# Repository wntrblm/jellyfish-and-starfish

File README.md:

# Jellyfish & Starfish

Jellyfish and Starfish are control boards designed for use with the LumenPnP. Starfish controls the base of the machine including X & Y axes and pneumatics. Jellyfish controls the head of the machine including the Z, A, and B axes.

## No support

Jellyfish and Starfish were made for Winterbloom's internal use cases and we don't have the resources to provide support. While we hope that this repository contains useful information for you, please note that issues and pull requests may go unanswered or may be closed without reply.

## License

Jellyfish and Starfish are open source, however, licensing a project like this is a little complicated. Please take a chance to review the [LICENSE](LICENSE.md) file.

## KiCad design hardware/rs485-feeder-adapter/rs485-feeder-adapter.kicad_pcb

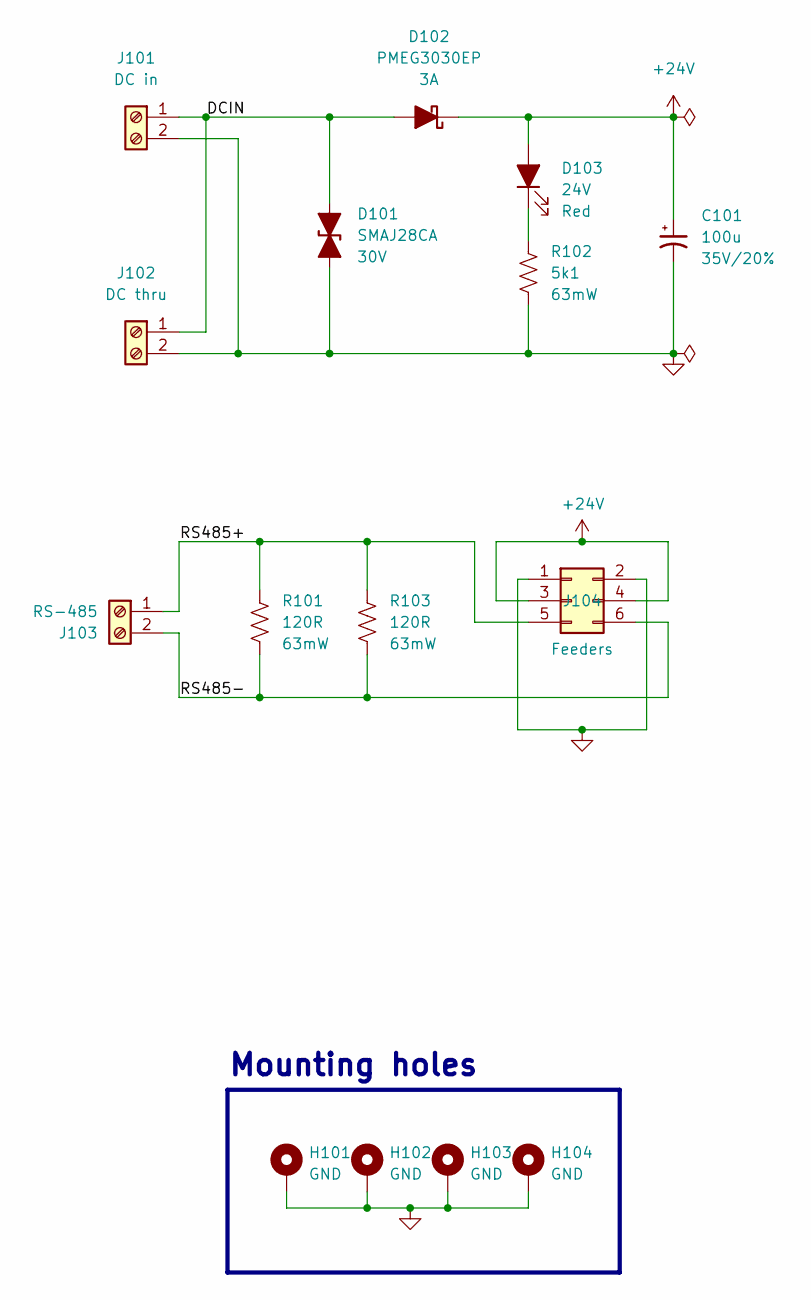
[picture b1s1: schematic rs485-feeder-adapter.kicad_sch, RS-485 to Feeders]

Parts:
C101: 100u; CP_Elec_6.3x9.9; Rating 35V/20%; mpn 865080653016, UWT1V221MNL1GS
D101: SMAJ28CA; D_SMA; Rating 30V; mpn SMAJ28CA
D102: PMEG3030EP; D_SOD-128; Rating 3A; mpn PMEG3030EP,115
D103: 24V; LED_0805_Kingbright_APT2012; Rating Red; mpn APT2012EC
H101, H102, H103, H104: GND; MountingHole_3mm_Pad
J101: DC in; TerminalBlock_CUI_TB002-500_1x02_P5.00mm_Vertical; mpn TB002-500-02BE
J102: DC thru; TerminalBlock_CUI_TB002-500_1x02_P5.00mm_Vertical; mpn TB002-500-02BE
J103: RS-485; TerminalBlock_4UCON_1x02_P3.50mm_Horizontal
J104: Feeders; IDC-Header_2x03_P2.54mm_Vertical
R101, R103: 120R; R_0402_HandSolder; Rating 63mW; mpn CRGCQ0402F120R
R102: 5k1; R_0402_HandSolder; Rating 63mW; mpn AC0603FR-075K1L

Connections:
+24V: C101.1, D102.1 (K), D103.2 (A), J104.3, J104.4
/DCIN: D101.1 (A1), D102.2 (A), J101.1, J102.1
/RS485+: J103.1, J104.5, R101.1, R103.1
/RS485-: J103.2, J104.6, R101.2, R103.2
GND: C101.2, D101.2 (A2), H101.1, H102.1, H103.1, H104.1, J101.2, J102.2, J104.1, J104.2, R102.2
unnamed: D103.1 (K), R102.1

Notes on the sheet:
Mounting holes

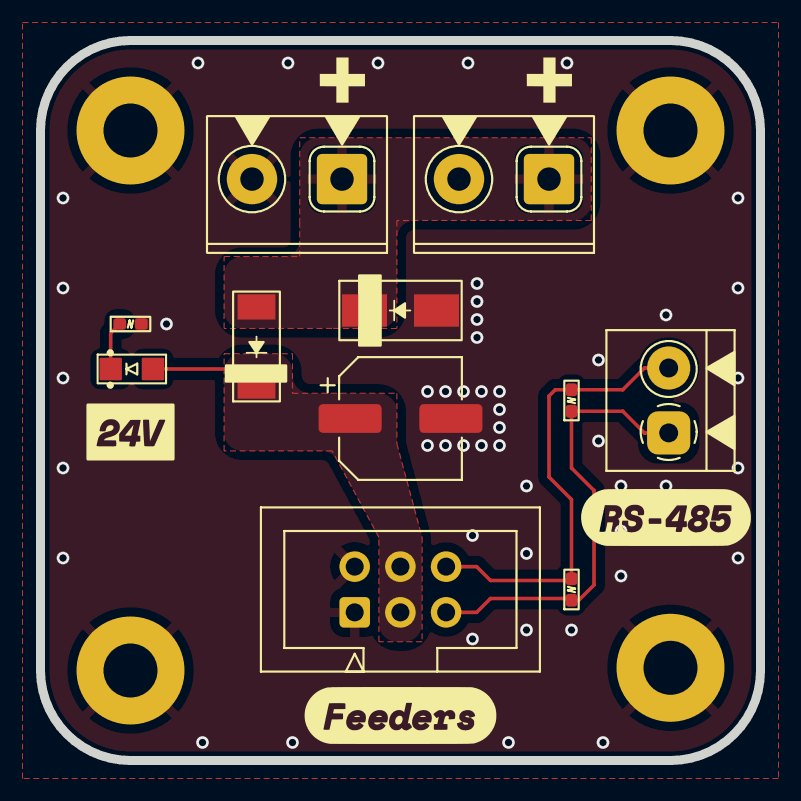
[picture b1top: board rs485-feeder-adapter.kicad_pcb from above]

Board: 2 copper layers, 40.0 x 40.0 mm, 15 parts (0 on the bottom side), 6 nets.

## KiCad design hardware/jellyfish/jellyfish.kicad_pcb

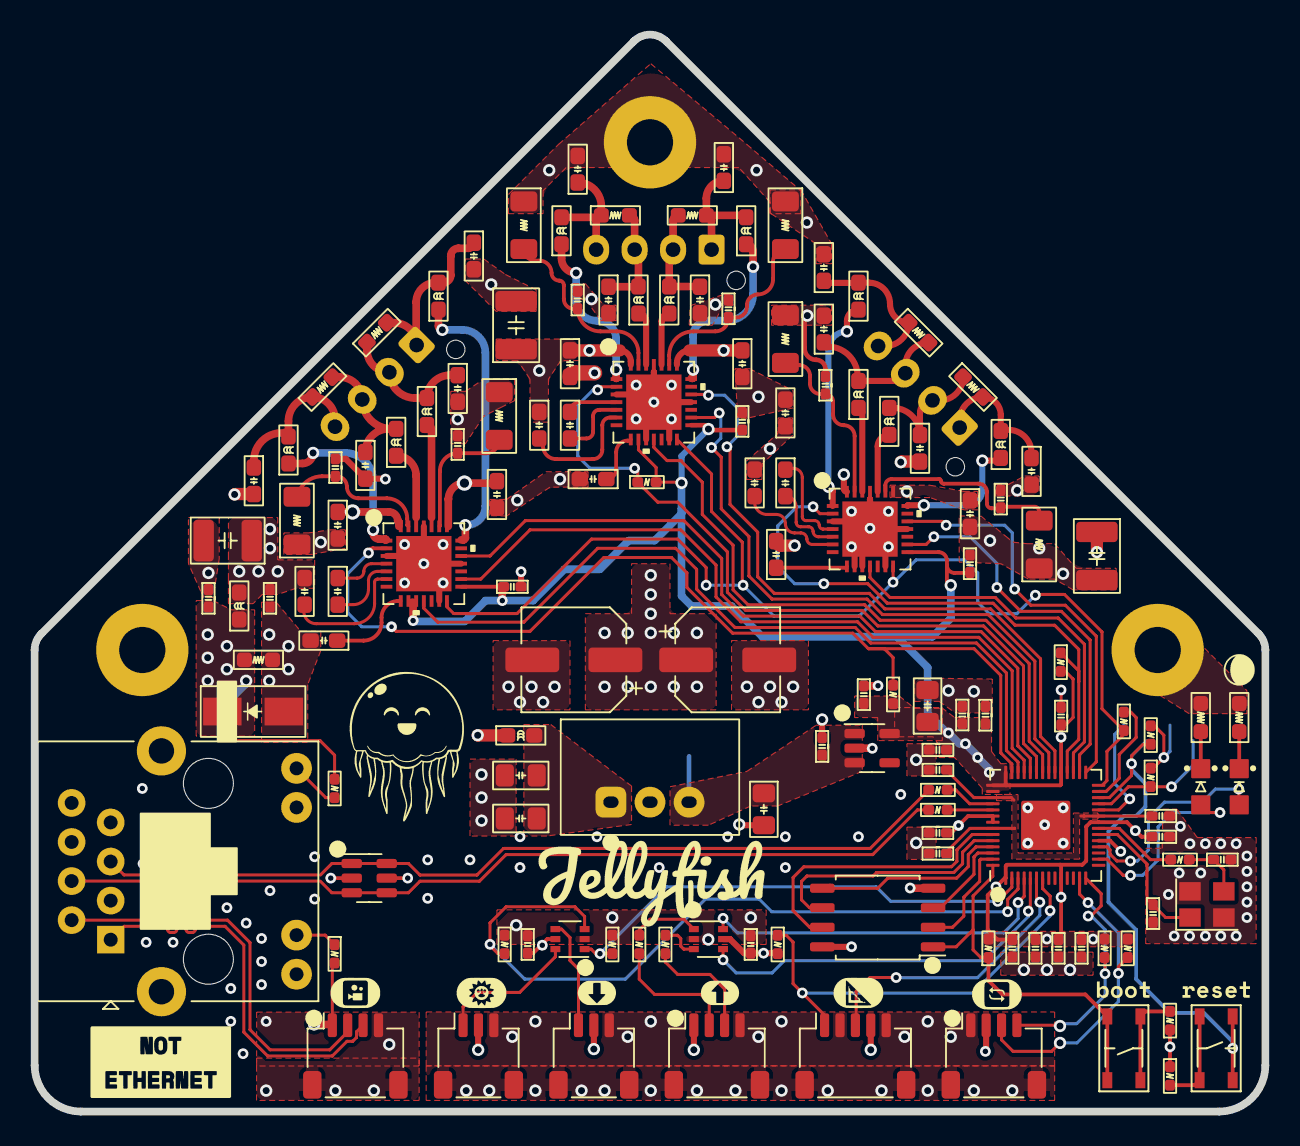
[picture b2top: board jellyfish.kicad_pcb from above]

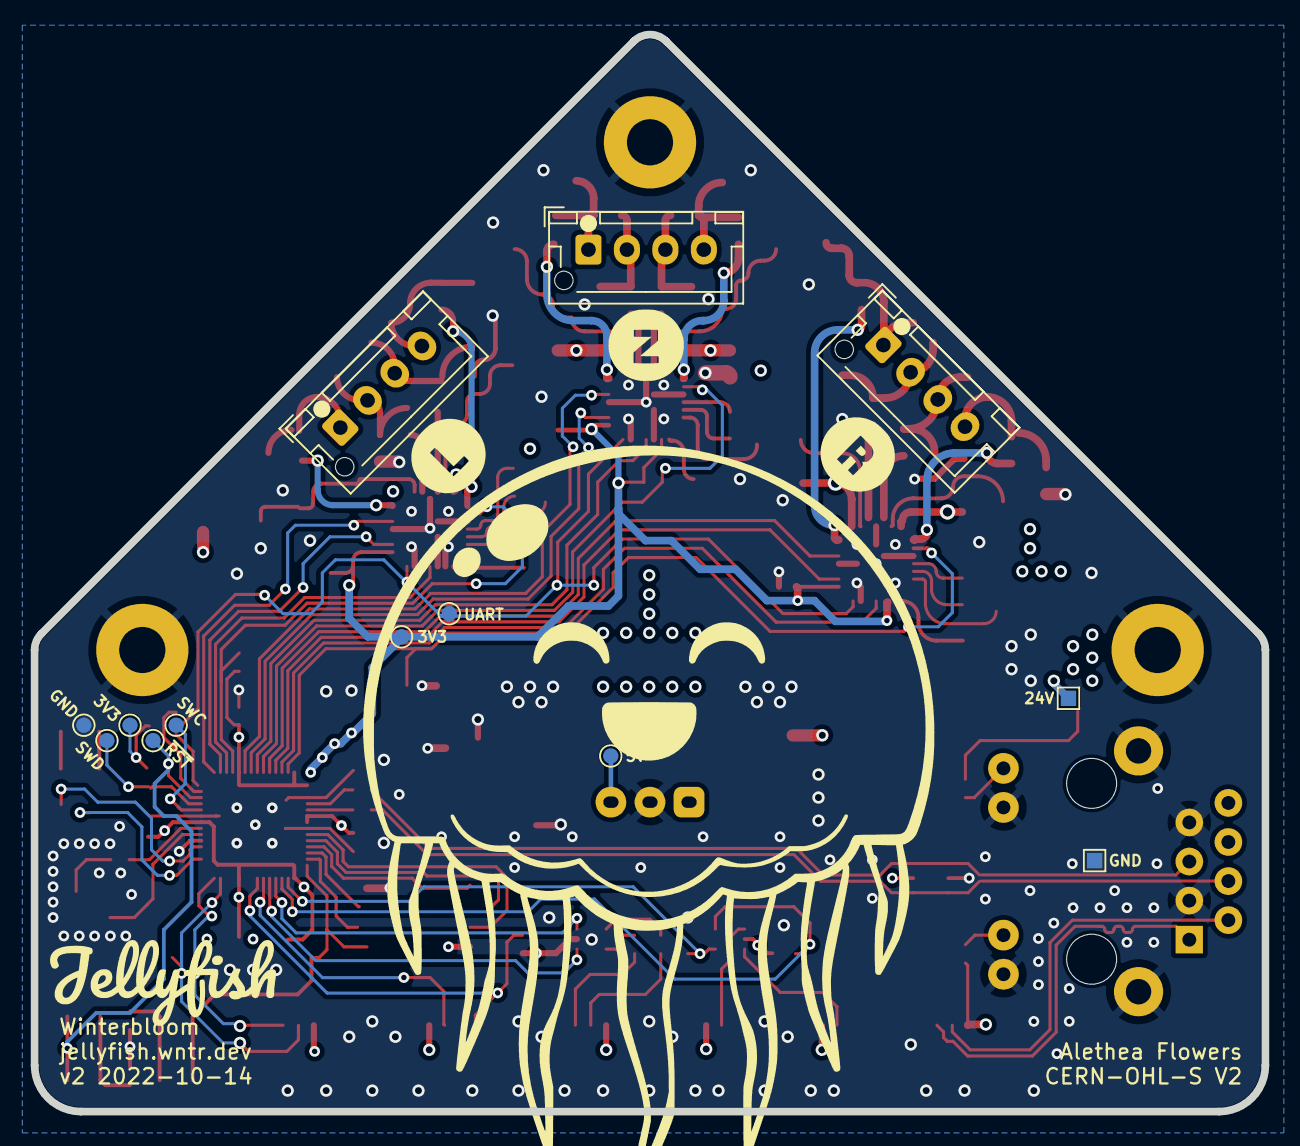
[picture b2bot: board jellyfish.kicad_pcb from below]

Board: 4 copper layers, 80.0 x 70.0 mm, 155 parts (13 on the bottom side), 103 nets.

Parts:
C1, C8, C9, C11, C12, C13, C14, C15, C16, C17, C20, C21, C25, C27, C29, C32, C33, C43, C46, C47, C57, C60, C61: 100n; C_0402_HandSolder
C2: 4.7u; C_0805_HandSolder
C3, C4: 22u; C_0805_HandSolder
C5, C22: 100u; CP_Elec_6.3x7.7
C6, C7, C18, C19, C26: 1u; C_0402_HandSolder
C10: 10u; C_0805_HandSolder
C23, C24: 15p; C_0402_HandSolder
C28, C42, C56: 22n; C_0603_HandSolder
C30, C36, C37, C44, C50, C51, C58, C64, C65: 100n; C_0603_HandSolder
C31, C45, C59: 4.7u; C_0603_HandSolder
C35, C49, C63: 10u; C_1210_HandSolder
C38, C39, C40, C41, C52, C53, C54, C55, C66, C67, C68, C69: 470p; C_0603_HandSolder
D1: AUX; LED_0805_Kingbright_APT2012
D2: SMAJ28A; D_SMA
D4: ACT; LED_0805_Kingbright_APT2012
FB1, FB2, FB3, FB4, FB5, FB6, FB7, FB8, FB9, FB10, FB11, FB12, FB13, FB14: 50Ω @ 100MHz; L_0603_HandSolder
H1, H2, H3: GND; MountingHole_3mm_Pad
J1: INS; JST_SH_SM04B-SRSS-TB_1x04-1MP_P1.00mm_Horizontal
J2: 8P8C_LED_Shielded; RJ45_Amphenol_RJE45-188-1411_Vertical
J3: CAM; JST_SH_SM04B-SRSS-TB_1x04-1MP_P1.00mm_Horizontal
J4: CAMLED; JST_SH_SM03B-SRSS-TB_1x03-1MP_P1.00mm_Horizontal
J5: OUT1; JST_SH_SM03B-SRSS-TB_1x03-1MP_P1.00mm_Horizontal
J6: BLTOUCH; JST_SH_SM05B-SRSS-TB_1x05-1MP_P1.00mm_Horizontal
J7, J8, J9: MOTOR; JST_XH_B4B-XH-AM_1x04_P2.50mm_Vertical
J10: Stemma QT; JST_SH_SM04B-SRSS-TB_1x04-1MP_P1.00mm_Horizontal
R1, R2, R15, R26, R27: 5.1k; R_0402_HandSolder
R3, R16: 100; R_0402_HandSolder
R4, R5, R12, R13, R14, R17, R20, R23: 10k; R_0402_HandSolder
R6, R7: 27R; R_0402_HandSolder
R8, R9, R11, R29: 1k; R_0402_HandSolder
R10, R28: 1k; R_0603_HandSolder
R18, R19, R21, R22, R24, R25: 220m; R_1206_HandSolder
RV1, RV2, RV3, RV4, RV5, RV6, RV7: 35V; R_0603_HandSolder
SW1: BOOTSEL; Tactile_Switch_4.2mm
SW2: RESET; Tactile_Switch_4.2mm
TP1: GND; TestPoint_Pad_1.0x1.0mm
TP2: 24V; TestPoint_Pad_1.0x1.0mm
TP3: 5V; TestPoint_Pad_D1.0mm
TP4, TP6: 3V3; TestPoint_Pad_D1.0mm
TP5: GND; TestPoint_Pad_D1.0mm
TP7: ~{RST}; TestPoint_Pad_D1.0mm
TP8: SWD; TestPoint_Pad_D1.0mm
TP9: SWC; TestPoint_Pad_D1.0mm
TP17: UART; TestPoint_Pad_D1.0mm
U1: VX7805-500; Converter_DCDC_CUI_VX78-500_THT
U2: MIC5317-3.3; SOT-23-5
U3: RP2040; RP2040-QFN-56
U4: W25Q128JVS; SOIC-8_5.23x5.23mm_P1.27mm
U5, U7: 74HC2G34; SOT-363_SC-70-6
U6: TVS; SOT-23-6
U8, U9, U10: TMC2209; TMC2209-LA
Y1: 12MHz; Crystal_SMD_Abracon_ABM8G-4Pin_3.2x2.5mm

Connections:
+1V1: C19.1, C20.1, C21.1, U3.23 (DVDD), U3.45 (VREG_VOUT), U3.50 (DVDD)
+3V3: C1.1, C7.1, C10.1, C11.1, C12.1, C13.1, C14.1, C15.1, C16.1, C17.1, C18.1, C25.1, C26.1, C29.1, C43.1, C57.1, J10.2, R4.2, R5.1, R12.2, R15.2, R17.2, R20.2, R23.2, R26.2, R27.2, TP4.1, TP6.1, U2.5 (OUT), U3.1 (IOVDD), U3.10 (IOVDD), U3.22 (IOVDD), U3.33 (IOVDD), U3.42 (IOVDD), U3.43 (ADC_AVDD), U3.44 (VREG_IN), U3.48 (USB_VDD), U3.49 (IOVDD), U4.8 (VCC), U5.5 (VCC), U8.15 (VCC_IO), U9.9 (MS1_AD0), U9.15 (VCC_IO), U10.9 (MS1_AD0), U10.10 (MS2_AD1), U10.15 (VCC_IO)
+5V: C4.1, C6.1, C27.1, J1.1, J3.1, J4.2, J5.2, J6.4, R1.2, TP3.1, U1.3 (Vout), U2.1 (IN), U2.3 (EN), U6.5 (VBUS), U7.5 (VCC)
+24V: C5.1, C9.1, C22.1, C30.1, C35.1, C36.1, C37.1, C44.1, C49.1, C50.1, C51.1, C58.1, C63.1, C64.1, C65.1, FB1.2, U8.22 (VS), U8.28 (VS), U9.22 (VS), U9.28 (VS), U10.22 (VS), U10.28 (VS)
/Connections/AUX_OUT: R14.2, U3.3 (GPIO1), U7.3 (2A)
/Connections/BLTOUCH_CONTROL: J6.3, U3.6 (GPIO4)
/Connections/BLTOUCH_OUT: J6.1, R15.1, U3.7 (GPIO5)
/Connections/CAM_D+: J2.1, J3.3
/Connections/CAM_D-: J2.2, J3.2
/Connections/CAM_LED: R13.2, U3.2 (GPIO0), U7.1 (1A)
/Connections/IN_1: U3.4 (GPIO2), U5.6 (1Y)
/Connections/IN_2: U3.5 (GPIO3), U5.4 (2Y)
/Connections/MCU_D+: J2.4, R6.1, U6.3 (D+), U6.4 (D+)
/Connections/MCU_D-: J2.5, R7.1, U6.1 (D-), U6.6 (D-)
/Connections/QWIIC_SCL: J10.4, R27.1, U3.14 (GPIO11)
/Connections/QWIIC_SDA: J10.3, R26.1, U3.13 (GPIO10)
/Left Motor/5VOUT: C31.1, U8.8 (5VOUT)
/Left Motor/BRA: C33.1, R19.2, U8.23 (BRA)
/Left Motor/BRB: C32.1, R18.2, U8.27 (BRB)
/Left Motor/CPI: C28.2, U8.5 (CPI)
/Left Motor/CPO: C28.1, U8.4 (CPO)
/Left Motor/DIAG: U3.31 (GPIO20), U8.11 (DIAG)
/Left Motor/DIR: U3.29 (GPIO18), U8.19 (DIR)
/Left Motor/ENN: R17.1, U3.32 (GPIO21), U8.2 (ENN)
/Left Motor/OA1: FB4.1, U8.24 (OA1)
/Left Motor/OA2: FB5.1, U8.21 (OA2)
/Left Motor/OB1: FB3.1, U8.26 (OB1)
/Left Motor/OB2: FB2.1, U8.1 (OB2)
/Left Motor/STEP: U3.30 (GPIO19), U8.16 (STEP)
/Left Motor/VCP: C30.2, U8.6 (VCP)
/Microcontroller/ACT_LED: D4.2 (A), U3.18 (GPIO15)
/Microcontroller/AUX_LED: D1.2 (A), U3.16 (GPIO13)
/Microcontroller/M1_DIAG: U3.36 (GPIO24), U9.11 (DIAG)
/Microcontroller/M1_DIR: U3.34 (GPIO22), U9.19 (DIR)
/Microcontroller/M1_EN: R20.1, U3.37 (GPIO25), U9.2 (ENN)
/Microcontroller/M1_STEP: U3.35 (GPIO23), U9.16 (STEP)
/Microcontroller/M2_DIAG: U3.40 (GPIO28_ADC2), U10.11 (DIAG)
/Microcontroller/M2_DIR: U3.38 (GPIO26_ADC0), U10.19 (DIR)
/Microcontroller/M2_EN: R23.1, U3.41 (GPIO29_ADC3), U10.2 (ENN)
/Microcontroller/M2_STEP: U3.39 (GPIO27_ADC1), U10.16 (STEP)
/Microcontroller/QSPI_CS: R12.1, SW1.1, U3.56 (QSPI_SS), U4.1 (~CS)
/Microcontroller/QSPI_SCLK: U3.52 (QSPI_SCLK), U4.6 (CLK)
/Microcontroller/QSPI_SD0: U3.53 (QSPI_SD0), U4.5 (DI(IO0))
/Microcontroller/QSPI_SD1: U3.55 (QSPI_SD1), U4.2 (DO(IO1))
/Microcontroller/QSPI_SD2: U3.54 (QSPI_SD2), U4.3 (IO2)
/Microcontroller/QSPI_SD3: U3.51 (QSPI_SD3), U4.7 (IO3)
/Microcontroller/RUN: R4.1, SW2.1, TP7.1, U3.26 (RUN)
/Microcontroller/SWCLK: TP9.1, U3.24 (SWCLK)
/Microcontroller/SWD: R5.2, TP8.1, U3.25 (SWD)
/Microcontroller/UART1_TX: R8.1, U3.27 (GPIO16)
/Microcontroller/USB_D+: R6.2, U3.47 (USB_DP)
/Microcontroller/USB_D-: R7.2, U3.46 (USB_DM)
/Microcontroller/XIN: C23.1, U3.20 (XIN), Y1.1
/Microcontroller/XOUT: R11.1, U3.21 (XOUT)
/Power/VIN_FILTERED: C2.1, C3.1, FB14.2, U1.1 (Vin)
/Right Motor/5VOUT: C59.1, U10.8 (5VOUT)
/Right Motor/BRA: C61.1, R25.2, U10.23 (BRA)
/Right Motor/BRB: C60.1, R24.2, U10.27 (BRB)
/Right Motor/CPI: C56.2, U10.5 (CPI)
/Right Motor/CPO: C56.1, U10.4 (CPO)
/Right Motor/OA1: FB12.1, U10.24 (OA1)
/Right Motor/OA2: FB13.1, U10.21 (OA2)
/Right Motor/OB1: FB11.1, U10.26 (OB1)
/Right Motor/OB2: FB10.1, U10.1 (OB2)
/Right Motor/VCP: C58.2, U10.6 (VCP)
/TMC_UART: R8.2, TP17.1, U3.28 (GPIO17), U8.14 (PDN_UART), U9.14 (PDN_UART), U10.14 (PDN_UART)
/Z Motor/5VOUT: C45.1, U9.8 (5VOUT)
/Z Motor/BRA: C47.1, R22.2, U9.23 (BRA)
/Z Motor/BRB: C46.1, R21.2, U9.27 (BRB)
/Z Motor/CPI: C42.2, U9.5 (CPI)
/Z Motor/CPO: C42.1, U9.4 (CPO)
/Z Motor/OA1: FB8.1, U9.24 (OA1)
/Z Motor/OA2: FB9.1, U9.21 (OA2)
/Z Motor/OB1: FB7.1, U9.26 (OB1)
/Z Motor/OB2: FB6.1, U9.1 (OB2)
/Z Motor/VCP: C44.2, U9.6 (VCP)
GND: C1.2, C2.2, C3.2, C4.2, C5.2, C6.2, C7.2, C8.2, C9.2, C10.2, C11.2, C12.2, C13.2, C14.2, C15.2, C16.2, C17.2, C18.2, C19.2, C20.2, C21.2, C22.2, C23.2, C24.2, C25.2, C26.2, C27.2, C29.2, C31.2, C32.2, C33.2, C35.2, C36.2, C37.2, C38.2, C39.2, C40.2, C41.2, C43.2, C45.2, C46.2, C47.2, C49.2, C50.2, C51.2, C52.2, C53.2, C54.2, C55.2, C57.2, C59.2, C60.2, C61.2, C63.2, C64.2, C65.2, C66.2, C67.2, C68.2, C69.2, D2.2 (A), H1.1, H2.1, H3.1, J1.4, J1.MP (MountPin), J2.3, J2.7, J2.9, J2.11, J2.SH, J3.4, J3.MP (MountPin), J4.3, J4.MP (MountPin), J5.3, J5.MP (MountPin), J6.2, J6.5, J6.MP (MountPin), J10.1, J10.MP (MountPin), R9.1, R10.2, R13.1, R14.1, R18.1, R19.1, R21.1, R22.1, R24.1, R25.1, R28.2, R29.1, RV1.2, TP1.1, TP5.1, U1.2 (GND), U2.2 (GND), U3.19 (TESTEN), U3.57 (GND), U4.4 (GND), U5.2 (GND), U6.2 (GND), U7.2 (GND), U8.3 (GND), U8.9 (MS1_AD0), U8.10 (MS2_AD1), U8.13 (CLK), U8.18 (GND), U8.25 (GND), U8.29 (PAD), U9.3 (GND), U9.10 (MS2_AD1), U9.13 (CLK), U9.18 (GND), U9.25 (GND), U9.29 (PAD), U10.3 (GND), U10.13 (CLK), U10.18 (GND), U10.25 (GND), U10.29 (PAD), Y1.2, Y1.4
unnamed: C24.1, R11.2, Y1.3
unnamed: C38.1, FB3.2, J7.3, RV2.2
unnamed: C39.1, FB5.2, J7.1, RV3.2
unnamed: C40.1, FB2.2, J7.4, RV2.1
unnamed: C41.1, FB4.2, J7.2, RV3.1
unnamed: C52.1, FB7.2, J8.3, RV4.2
unnamed: C53.1, FB9.2, J8.1, RV5.2
unnamed: C54.1, FB6.2, J8.4, RV4.1
unnamed: C55.1, FB8.2, J8.2, RV5.1
unnamed: C66.1, FB11.2, J9.3, RV6.2
unnamed: C67.1, FB13.2, J9.1, RV7.2
unnamed: C68.1, FB10.2, J9.4, RV6.1
unnamed: C69.1, FB12.2, J9.2, RV7.1
unnamed: D1.1 (K), R28.1
unnamed: D4.1 (K), R10.1
unnamed: J1.2, R3.2
unnamed: J1.3, R16.2
unnamed: J2.10, R1.1
unnamed: J2.12, R2.1
unnamed: J4.1, U7.6 (1Y)
unnamed: J5.1, U7.4 (2Y)
unnamed: R3.1, U5.1 (1A)
unnamed: R9.2, SW1.2
unnamed: R16.1, U5.3 (2A)
unnamed: R29.2, SW2.2
VDC: C8.1, D2.1 (K), FB1.1, FB14.1, J2.6, J2.8, R2.2, RV1.1, TP2.1

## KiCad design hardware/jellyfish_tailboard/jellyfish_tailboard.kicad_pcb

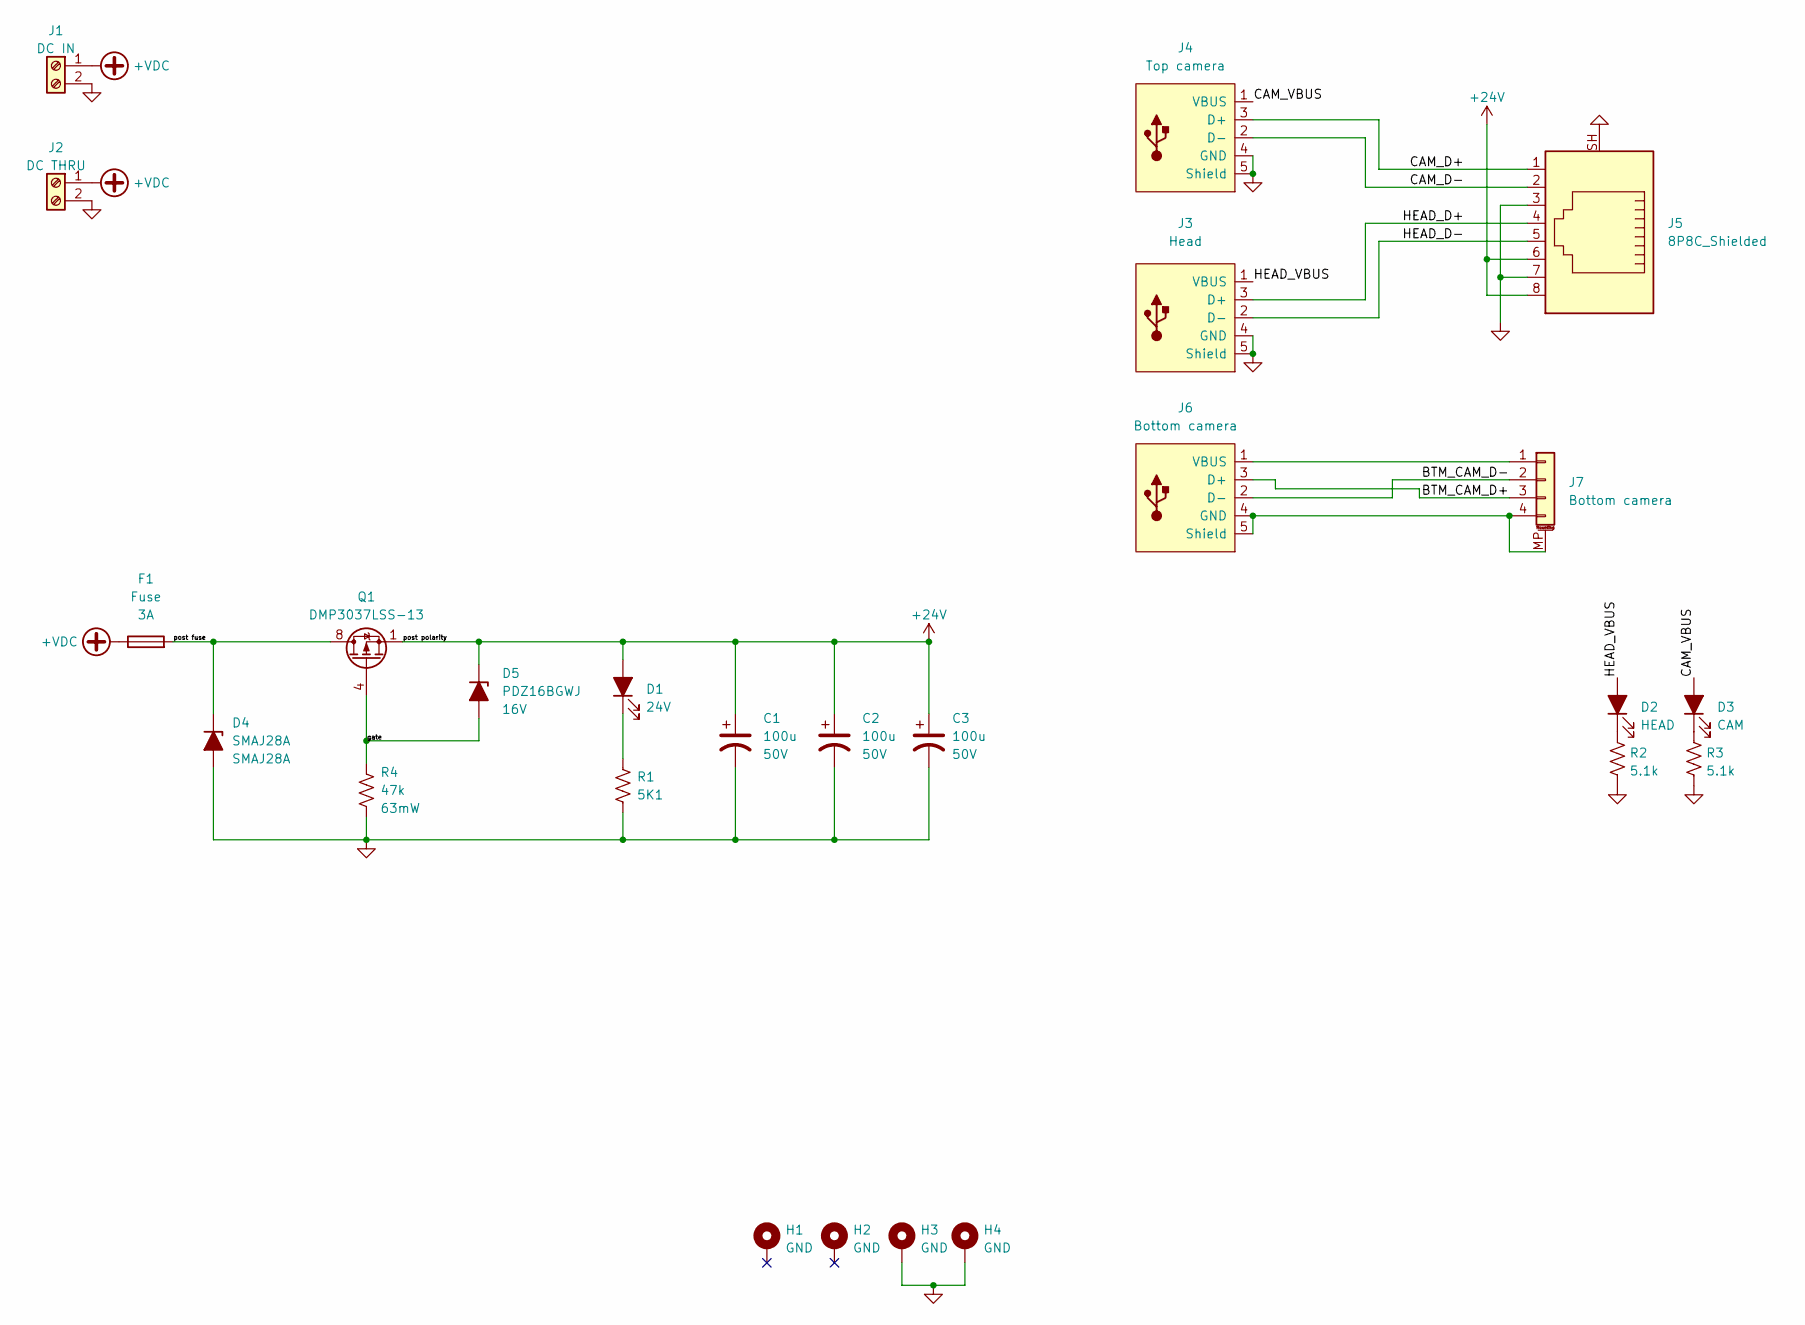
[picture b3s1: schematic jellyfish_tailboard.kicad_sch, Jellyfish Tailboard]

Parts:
C1, C2, C3: 100u; CP_Elec_6.3x9.9; Rating 50V
D1: 24V; LED_0805_Kingbright_APT2012; mpn APT2012EC
D2: HEAD; LED_0805_Kingbright_APT2012; mpn APT2012EC
D3: CAM; LED_0805_Kingbright_APT2012; mpn APT2012EC
D4: SMAJ28A; D_SMA; Rating 30V; mpn SMAJ28A
D5: PDZ16BGWJ; D_SOD-123; Rating 16V; mpn PDZ16BGWJ
F1: Fuse; Fuseholder_Blade_Mini_Keystone_3568; Rating 3A
H1, H2, H3, H4: GND; MountingHole_3mm_Pad
J1: DC IN; TerminalBlock_CUI_TB002-500_1x02_P5.00mm_Vertical; mpn TB002-500-02BE
J2: DC THRU; TerminalBlock_CUI_TB002-500_1x02_P5.00mm_Vertical; mpn TB002-500-02BE
J3: Head; USB_B_Receptacle_Horizontal; mpn 5787834-1
J4: Top camera; USB_B_Receptacle_Horizontal; mpn 5787834-1
J5: 8P8C_Shielded; Connector_RJ45_SS-7188S-A-PG4-BA-50
J6: Bottom camera; USB_B_Receptacle_Horizontal; mpn 5787834-1
J7: Bottom camera; JST_SH_SM04B-SRSS-TB_1x04-1MP_P1.00mm_Horizontal
Q1: DMP3037LSS-13; SOIC-8_3.9x4.9mm_P1.27mm
R1: 5K1; R_0402_HandSolder; mpn AC0603FR-075K1L
R2, R3: 5.1k; R_0402_HandSolder; mpn AC0603FR-075K1L
R4: 47k; R_0402_HandSolder; Rating 63mW; mpn RC0402FR-0747KL

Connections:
+24V: C1.1, C2.1, C3.1, D1.2 (A), D5.1 (K), J5.6, J5.8, Q1.1 (S), Q1.2 (S), Q1.3 (S)
+VDC: F1.1, J1.1, J2.1
/BTM_CAM_D+: J6.3 (D+), J7.3
/BTM_CAM_D-: J6.2 (D-), J7.2
/CAM_D+: J4.3 (D+), J5.1
/CAM_D-: J4.2 (D-), J5.2
/CAM_VBUS: D3.2 (A), J4.1 (VBUS)
/HEAD_D+: J3.3 (D+), J5.4
/HEAD_D-: J3.2 (D-), J5.5
/HEAD_VBUS: D2.2 (A), J3.1 (VBUS)
/gate: D5.2 (A), Q1.4 (G), R4.1
/post fuse: D4.1 (K), F1.2, Q1.5 (D), Q1.6 (D), Q1.7 (D), Q1.8 (D)
GND: C1.2, C2.2, C3.2, D4.2 (A), H3.1, H4.1, J1.2, J2.2, J3.4 (GND), J3.5 (Shield), J4.4 (GND), J4.5 (Shield), J5.3, J5.7, J5.SH, R1.2, R2.2, R3.2, R4.2
unnamed: D1.1 (K), R1.1
unnamed: D2.1 (K), R2.1
unnamed: D3.1 (K), R3.1
unnamed: J6.1 (VBUS), J7.1
unnamed: J6.4 (GND), J6.5 (Shield), J7.4, J7.MP (MountPin)

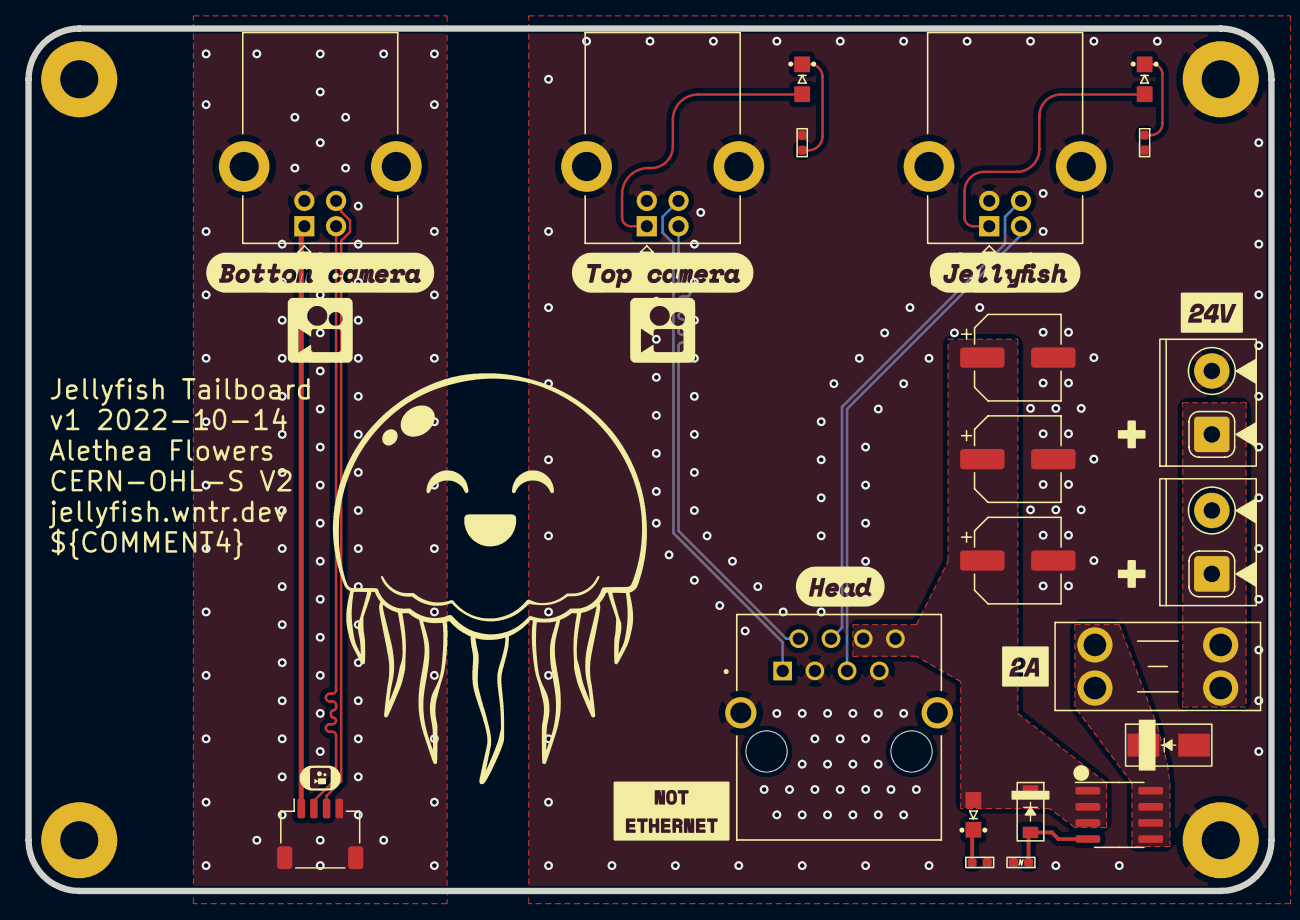
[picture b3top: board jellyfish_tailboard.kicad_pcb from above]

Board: 2 copper layers, 98.0 x 68.0 mm, 25 parts (0 on the bottom side), 18 nets.

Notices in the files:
hardware/breakouts/drv103_solenoid_driver_breakout/drv103_solenoid_driver_breakout.kicad_sch:
CERN-OHL-P V2
hardware/jellyfish/jellyfish.kicad_pcb:
CERN-OHL-S V2
